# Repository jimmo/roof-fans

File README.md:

# roof-fans
ESP8266 fan controller for roof cavity ventilation

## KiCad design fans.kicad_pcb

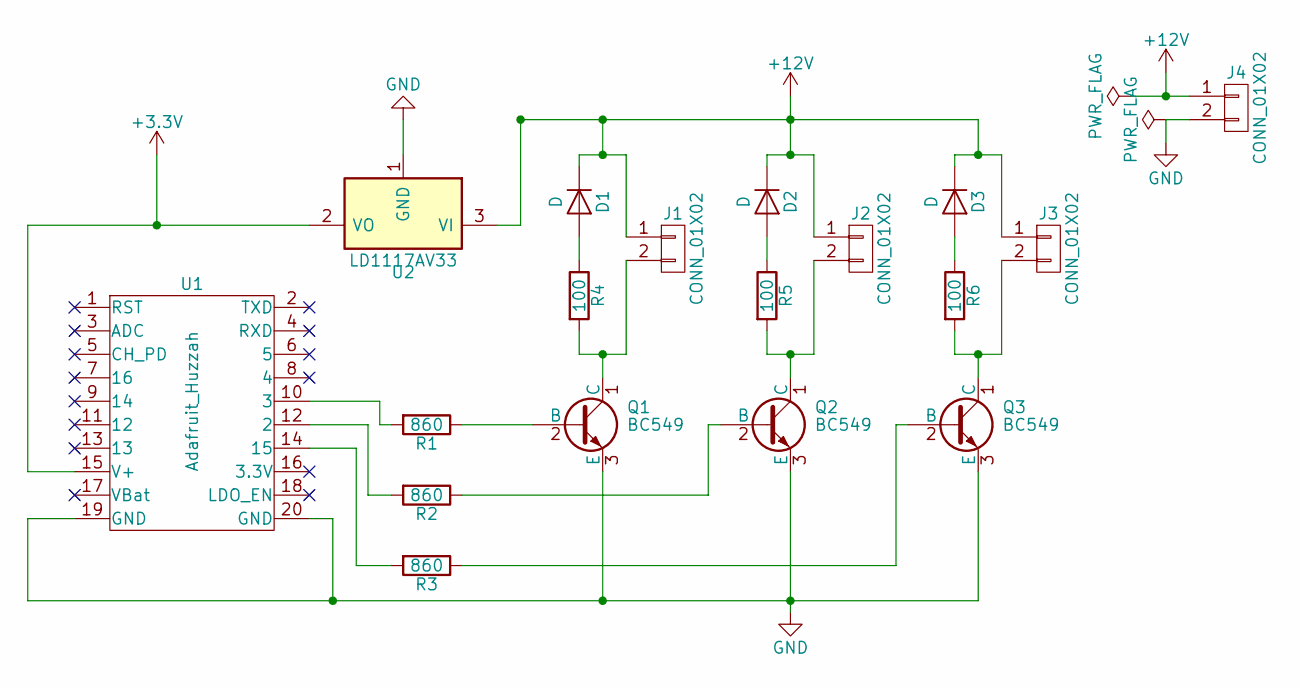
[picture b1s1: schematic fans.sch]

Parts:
D1, D2, D3: D; D_A-405_P7.62mm_Horizontal
J1, J2, J3, J4: CONN_01X02; Pin_Header_Straight_1x02_Pitch2.54mm
Q1, Q2, Q3: BC549; TO-92_Molded_Wide_Oval
R1, R2, R3: 860; R_Axial_DIN0207_L6.3mm_D2.5mm_P10.16mm_Horizontal
R4, R5, R6: 100; R_Axial_DIN0207_L6.3mm_D2.5mm_P10.16mm_Horizontal
U1: Adafruit_Huzzah; Adafruit_Huzzah_ESP8266_Breakout
U2: LD1117AV33; TO-220_Vertical

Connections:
+3V3: U1.15 (V+), U2.2 (VO)
+12V: D1.1 (K), D2.1 (K), D3.1 (K), J1.1, J2.1, J3.1, J4.1, U2.3 (VI)
GND: J4.2, Q1.3 (E), Q2.3 (E), Q3.3 (E), U1.19 (GND), U1.20 (GND), U2.1 (GND)
unnamed: D1.2 (A), R4.1
unnamed: D2.2 (A), R5.1
unnamed: D3.2 (A), R6.1
unnamed: J1.2, Q1.1 (C), R4.2
unnamed: J2.2, Q2.1 (C), R5.2
unnamed: J3.2, Q3.1 (C), R6.2
unnamed: Q1.2 (B), R1.1
unnamed: Q2.2 (B), R2.1
unnamed: Q3.2 (B), R3.1
unnamed: R1.2, U1.10 (3)
unnamed: R2.2, U1.12 (2)
unnamed: R3.2, U1.14 (15)

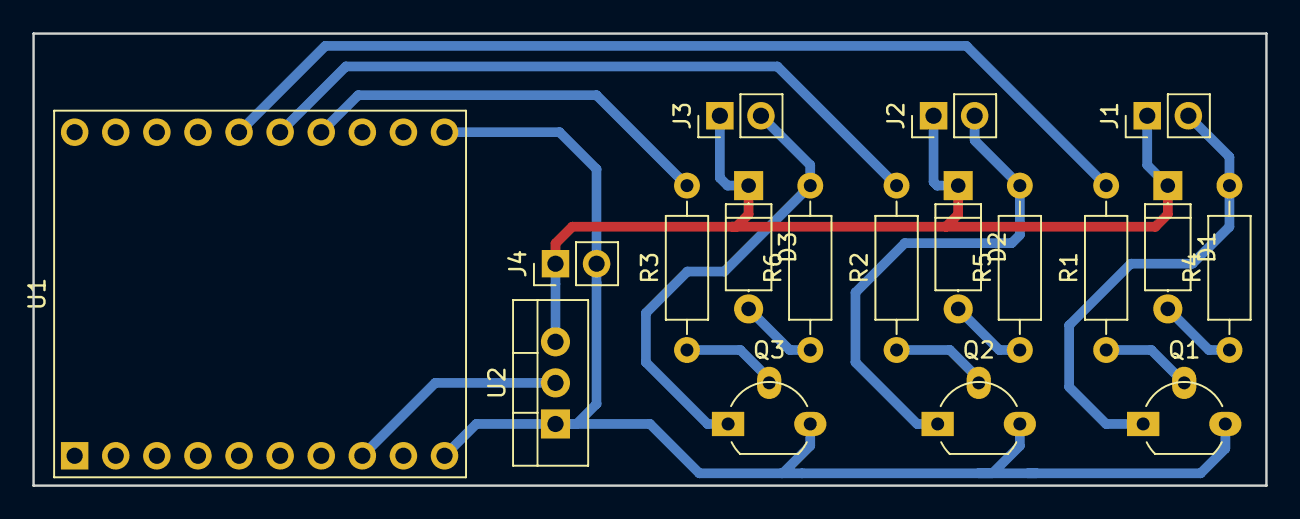
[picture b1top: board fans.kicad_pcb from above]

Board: 2 copper layers, 76.2 x 27.9 mm, 18 parts (0 on the bottom side), 15 nets.

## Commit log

2017-05-27 First layout
2017-05-27 Add footprint and layout
2017-05-27 First finished layout.
2017-05-28 Wider traces.
